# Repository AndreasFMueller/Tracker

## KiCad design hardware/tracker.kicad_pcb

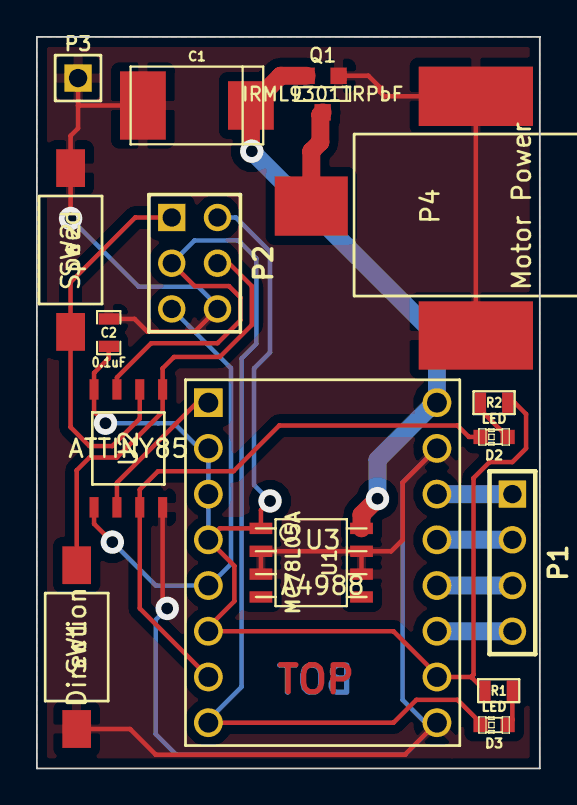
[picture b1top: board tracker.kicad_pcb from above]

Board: 2 copper layers, 27.9 x 40.6 mm, 16 parts (0 on the bottom side), 16 nets.

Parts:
C1: 100u; c_tant_D
C2: 0.1uF; SM0603_Capa
D2, D3: LED; LED-0603
P1: Motor; PIN_ARRAY_4x1
P2: ISP; pin_array_3x2
P3: GND; PIN_ARRAY_1
P4: Motor Power; Power
Q1: IRML9301TRPbF; SOT23GDS
R1: 470; SM0603
R2: 1k; SM0603
SW1: Direction; FSM-SM
SW2: Speed; FSM-SM
U1: MC78L05A; so-8
U2: ATTINY85; SOIC8W
U3: A4988

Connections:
+5V: C2.1, P2.2, R1.1, R2.1, U1.1, U2.8, U3.2, U3.3, U3.4, U3.6, U3.10
+12V: C1.1, Q1.S, U1.8, U3.16
GND: C1.2, C2.2, P2.6, P3.1, P4.2, Q1.G, SW1.2, SW2.2, U1.2, U1.3, U1.6, U1.7, U2.4, U3.9, U3.15
unnamed: P2.5, U2.1, U3.5
unnamed: P4.1, Q1.D
unnamed: D3.2, P2.3, U2.7, U3.8
unnamed: P2.4, SW1.1, U2.5
unnamed: U2.2, U3.1
unnamed: P2.1, SW2.1, U2.6
unnamed: D3.1, R1.2
unnamed: D2.2, U2.3, U3.7
unnamed: D2.1, R2.2
unnamed: P1.4, U3.11
unnamed: P1.1, U3.14
unnamed: P1.2, U3.13
unnamed: P1.3, U3.12

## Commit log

2015-08-08 add parts and software skeleton
2015-08-08 add hardware files
2015-08-08 bring hardware and software together
2015-08-08 first draft of the firmware
2015-08-09 software (mostly) complete
2015-08-09 set speed step
2015-08-13 add missing pcb file
2015-08-13 add new plastic parts
2015-11-17 improve documentation, fix PWM configuration (:-0)
2015-11-17 minor changes
2015-11-20 fix repeat command bug
2015-11-21 typos
2015-11-21 fix timing constants
2015-11-21 add stop to tracking
2015-11-22 reorganize the code (25% space saving!)
2015-11-22 turn of LED when timer is stopped
2015-11-23 fix direction_toggle function
2015-11-23 no timer output at startup
2015-11-23 move LED2 to STEP output
2015-11-23 add missing file to tracker.zip
